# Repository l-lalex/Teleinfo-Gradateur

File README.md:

# Teleinfo-Gradateur
pilotage de gradateur en fonction du papp de teleinfo, s'appuie fortement sur le code et la librairie de Charles Hallard

Collecte les informations de teleinfo et envoie des commandes impulsionnelles via optocoupleur sur un gradateur numérique.

Le but est de faire consommer par un chauffe-eau électrique type cumulus l'excédent d'électricité produit par des panneaux photovoltaïques.

On fait varier la puissance du chauffe-eau de manière à ce que le papp (puissance apparente) mesuré en téléinfo reste inférieure à 50 VA.

On utilise un gradateur numérique contrôlant la puissance de 0 à 100% que l'on pilote par impulsions, le nombre d'impulsions dépend de la puissance à réduire.

Interface WEB de suivi s'appuyant sur le wifi de l'ESP8366

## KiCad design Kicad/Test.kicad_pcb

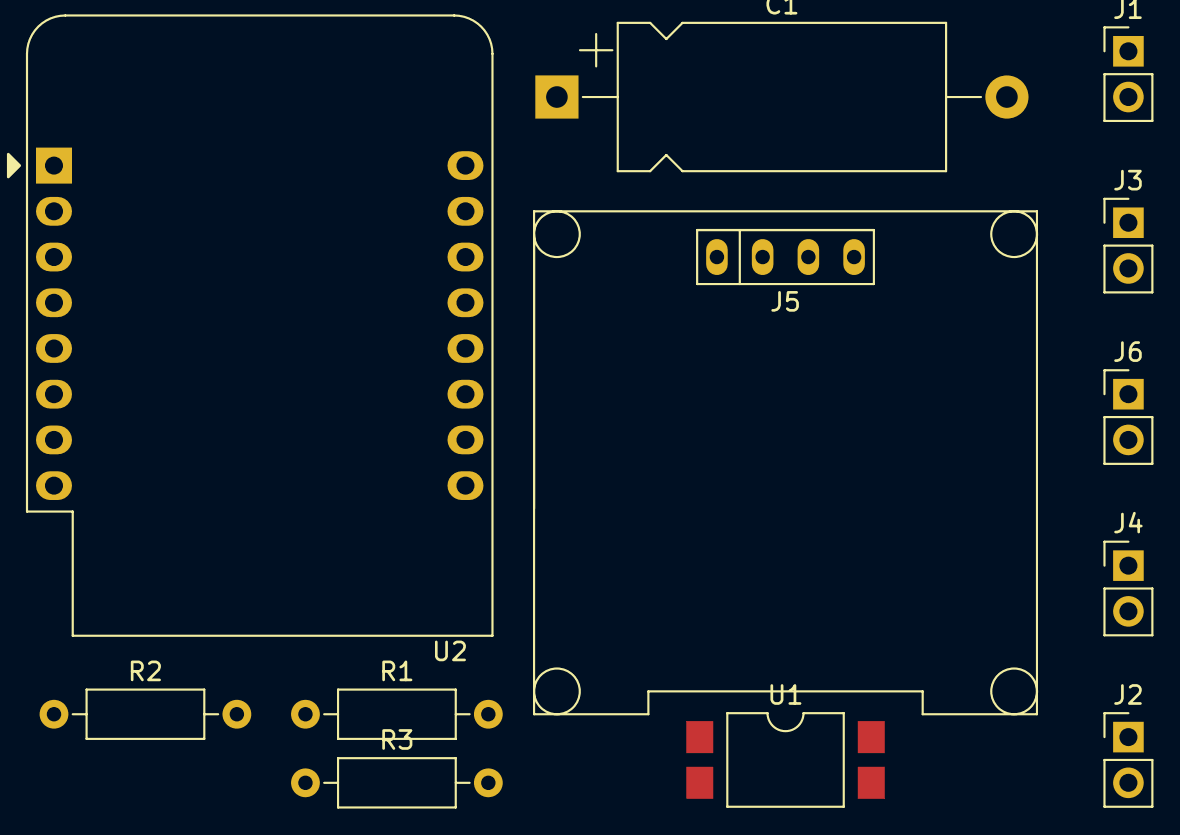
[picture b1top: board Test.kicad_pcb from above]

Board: 2 copper layers, 12 parts (0 on the bottom side), 13 nets, no tracks yet.

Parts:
C1: CP; CP_Axial_L18.0mm_D8.0mm_P25.00mm_Horizontal
J1: UP; PinHeader_1x02_P2.54mm_Vertical
J2: Teleinfo; PinHeader_1x02_P2.54mm_Vertical
J3: Down; PinHeader_1x02_P2.54mm_Vertical
J4: LED/LDR; PinHeader_1x02_P2.54mm_Vertical
J5: Oled
J6: Forcé; PinHeader_1x02_P2.54mm_Vertical
R1, R2: 200; R_Axial_DIN0207_L6.3mm_D2.5mm_P10.16mm_Horizontal
R3: 10K; R_Axial_DIN0207_L6.3mm_D2.5mm_P10.16mm_Horizontal
U1: SFH620A-2X007T; SMDIP-4_W9.53mm_Clearance8mm
U2: WeMos_D1_mini; WEMOS_D1_mini_light

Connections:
0V: J1.1, J3.1, J5.3, J6.1, U1.3, U2.10
unnamed: C1.2, J4.1, R2.1, U2.2
unnamed: J1.2, U2.4
unnamed: J2.1, R1.2
unnamed: J2.2, U1.2
unnamed: J3.2, U2.5
unnamed: J6.2, U2.12
unnamed: R1.1, U1.1
unnamed: R2.2, U2.3
unnamed: R3.2, U1.4, U2.6
SCL: J5.2, U2.14
SDA: J5.1, U2.13
VCC: C1.1, J4.2, J5.4, R3.1, U2.8

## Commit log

2021-04-30 Rename Wifinfo-smothled_oled_papp-carlos.ino to Wifinfo-oled_papp-gradateur-impulsion.ino
2021-05-12 Update Wifinfo-oled_papp-gradateur-impulsion.ino
    Ajout d'une routine d'impulsions en fonction de la puissance à réduire
2021-05-12 Add files via upload
    création du circuit imprimé associé
2021-05-12 nttoyage
    nettoyage
2021-05-13 Add files via upload
    schéma et pcb
